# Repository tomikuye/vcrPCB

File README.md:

# vcrPCB
KiCad PCB files and gerbers for custom PCB for Rice The Glove Team

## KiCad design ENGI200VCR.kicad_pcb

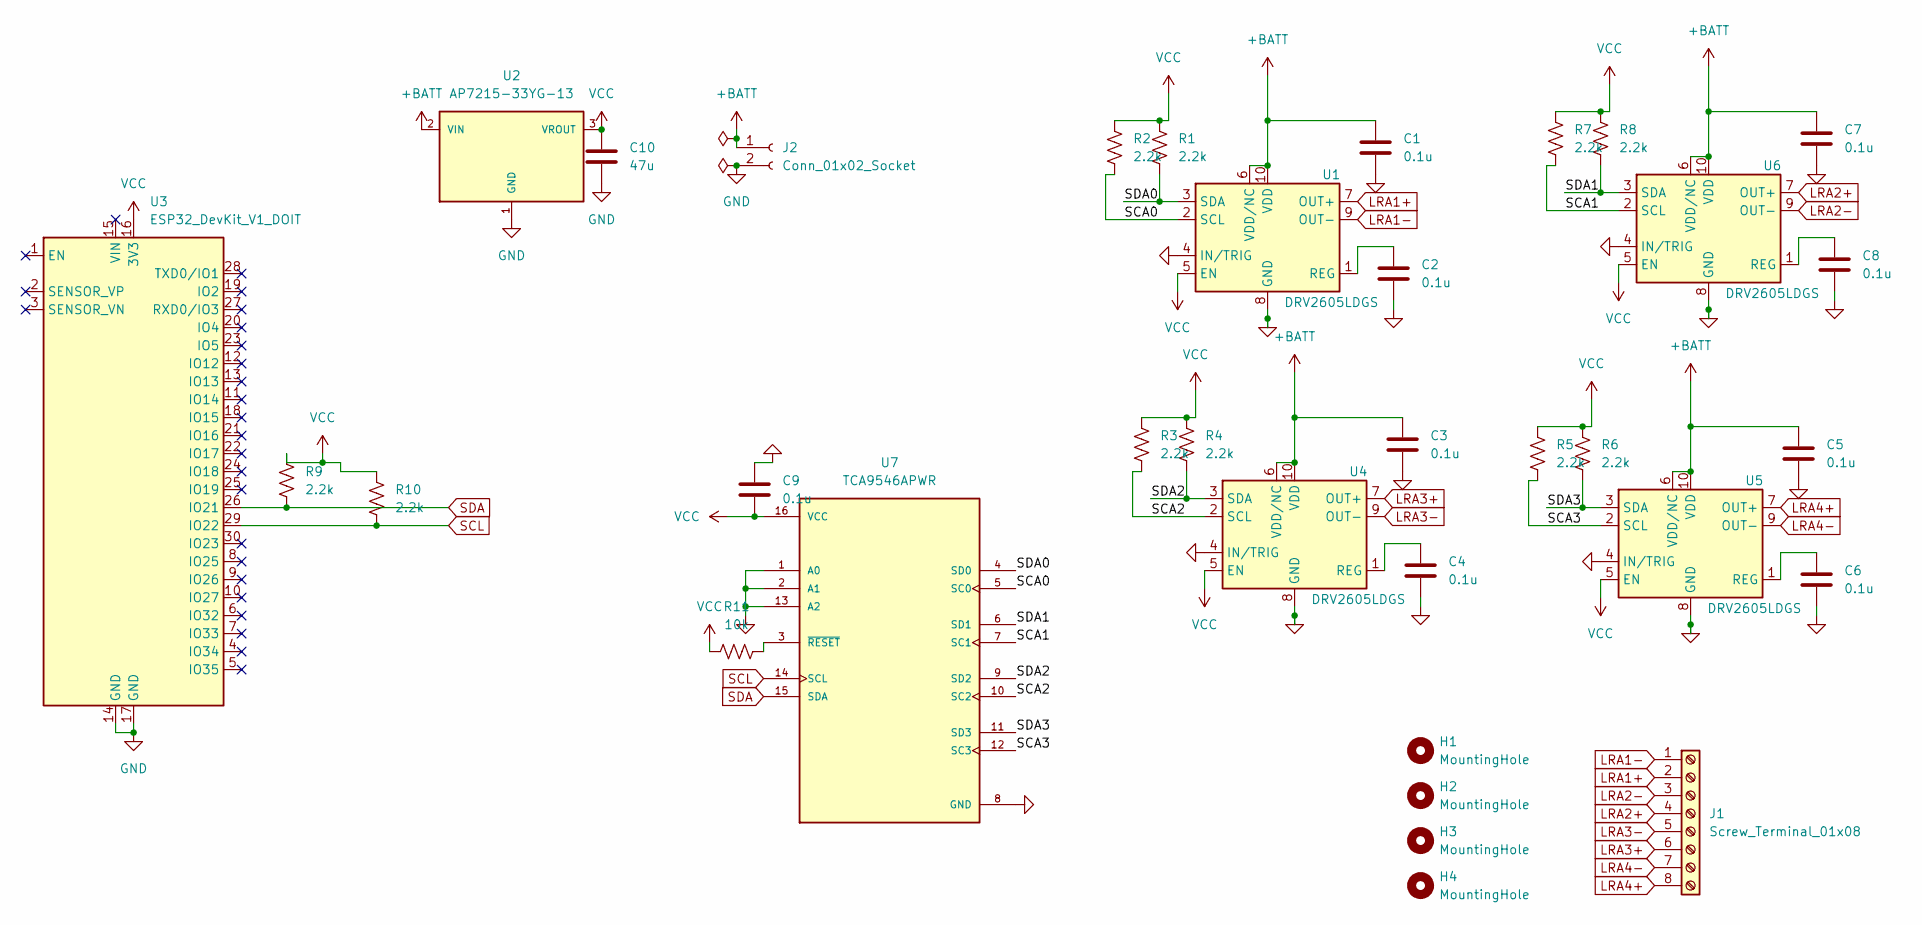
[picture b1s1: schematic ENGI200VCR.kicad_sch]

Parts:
C1, C2, C3, C4, C5, C6, C7, C8, C9: 0.1u; C_0402_1005Metric
C10: 47u; C_0805_2012Metric
H1, H2, H3, H4: MountingHole; MountingHole_2.2mm_M2
J1: Screw_Terminal_01x08; TerminalBlock_bornier-8_P5.08mm
J2: Conn_01x02_Socket; JST_EH_B2B-EH-A_1x02_P2.50mm_Vertical
R1, R2, R3, R4, R5, R6, R7, R8, R9, R10: 2.2k; R_0402_1005Metric
R11: 10k; R_0402_1005Metric
U1, U4, U5, U6: DRV2605LDGS; VSSOP-10_3x3mm_P0.5mm
U2: AP7215-33YG-13; SOT150P400X160-3N; MPN AP7215-33YG-13
U3: ESP32_DevKit_V1_DOIT; esp32_devkit_v1_doit
U7: TCA9546APWR; SOP65P640X120-16N; PARTREV B

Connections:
+BATT: C1.1, C3.1, C5.1, C7.1, J2.1, U1.6 (VDD/NC), U1.10 (VDD), U2.2 (VIN), U4.6 (VDD/NC), U4.10 (VDD), U5.6 (VDD/NC), U5.10 (VDD), U6.6 (VDD/NC), U6.10 (VDD)
/SCA0: R2.2, U1.2 (SCL), U7.5 (SC0)
/SCA1: R7.2, U6.2 (SCL), U7.7 (SC1)
/SCA2: R3.2, U4.2 (SCL), U7.10 (SC2)
/SCA3: R5.2, U5.2 (SCL), U7.12 (SC3)
/SDA0: R1.2, U1.3 (SDA), U7.4 (SD0)
/SDA1: R8.2, U6.3 (SDA), U7.6 (SD1)
/SDA2: R4.2, U4.3 (SDA), U7.9 (SD2)
/SDA3: R6.2, U5.3 (SDA), U7.11 (SD3)
GND: C1.2, C2.2, C3.2, C4.2, C5.2, C6.2, C7.2, C8.2, C9.1, C10.2, J2.2, U1.4 (IN/TRIG), U1.8 (GND), U2.1 (GND), U3.14 (GND), U3.17 (GND), U4.4 (IN/TRIG), U4.8 (GND), U5.4 (IN/TRIG), U5.8 (GND), U6.4 (IN/TRIG), U6.8 (GND), U7.1 (A0), U7.2 (A1), U7.8 (GND), U7.13 (A2); also elsewhere on the board
LRA1+: J1.2, U1.7 (OUT+)
LRA1-: J1.1, U1.9 (OUT-)
LRA2+: J1.4, U6.7 (OUT+)
LRA2-: J1.3, U6.9 (OUT-)
LRA3+: J1.6, U4.7 (OUT+)
LRA3-: J1.5, U4.9 (OUT-)
LRA4+: J1.8, U5.7 (OUT+)
LRA4-: J1.7, U5.9 (OUT-)
unnamed: C2.1, U1.1 (REG)
unnamed: C4.1, U4.1 (REG)
unnamed: C6.1, U5.1 (REG)
unnamed: C8.1, U6.1 (REG)
unnamed: R11.2, U7.3 (~RESET)
SCL: R10.2, U3.29 (IO22), U7.14 (SCL)
SDA: R9.2, U3.26 (IO21), U7.15 (SDA)
VCC: C9.2, C10.1, R1.1, R2.1, R3.1, R4.1, R5.1, R6.1, R7.1, R8.1, R9.1, R10.1, R11.1, U1.5 (EN), U2.3 (VROUT), U3.16 (3V3), U4.5 (EN), U5.5 (EN), U6.5 (EN), U7.16 (VCC); also elsewhere on the board

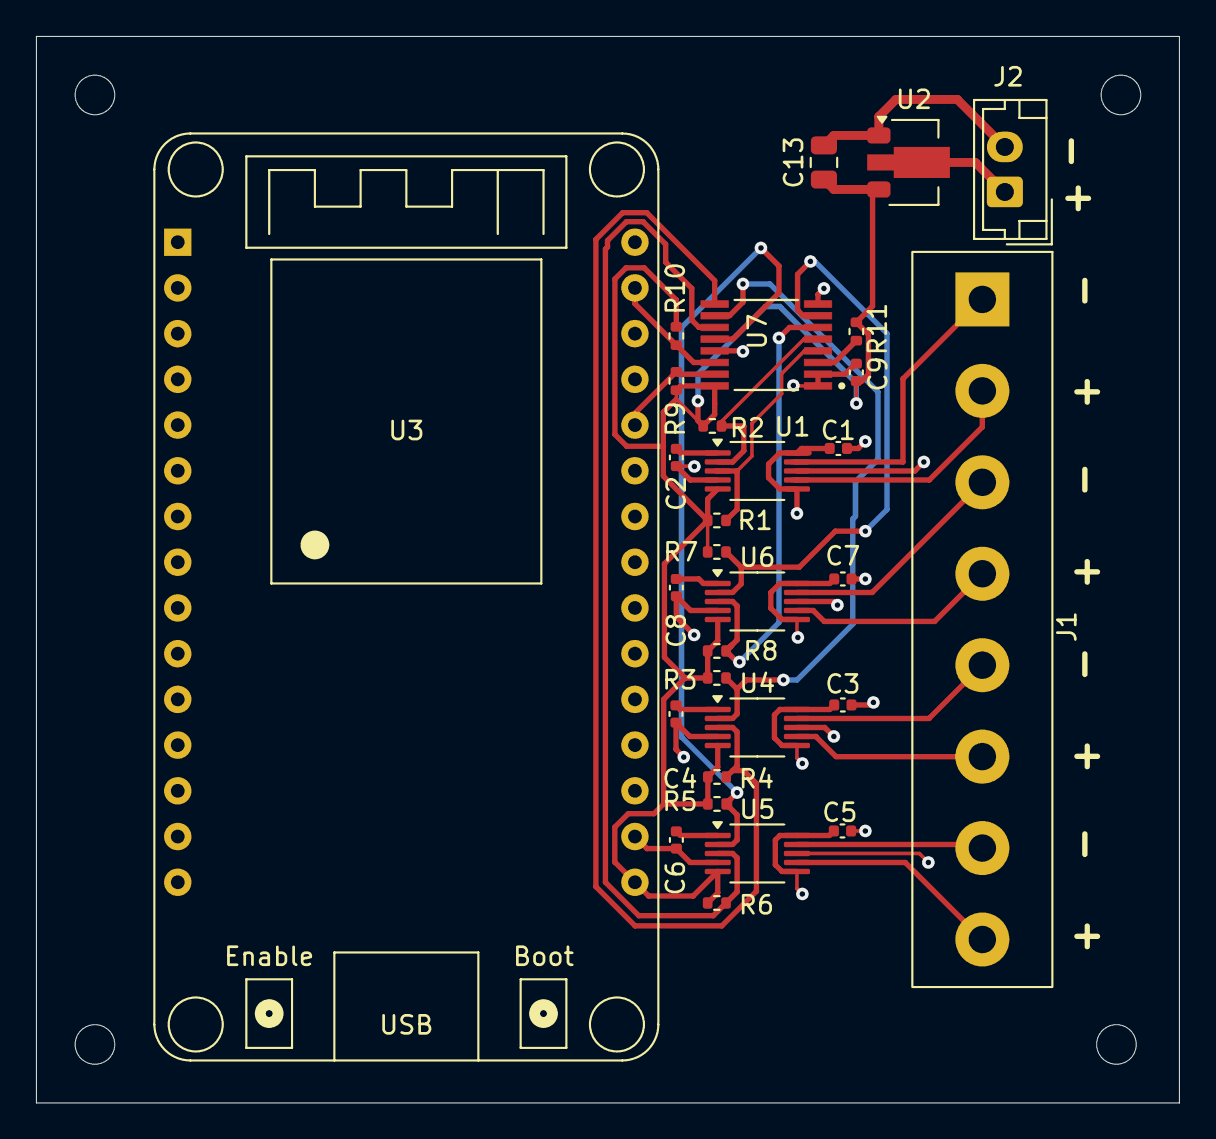
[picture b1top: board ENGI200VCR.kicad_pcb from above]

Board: 4 copper layers, 63.5 x 59.2 mm, 34 parts (0 on the bottom side), 26 nets.

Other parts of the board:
C13: 47u; C_0805_2012Metric

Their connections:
GND: C13.2; also elsewhere on the board
VCC: C13.1; also elsewhere on the board

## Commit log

2024-04-01 Rename Screenshot 2024-04-01 at 2.46.02 PM.png to 3DRenderofPCB
2024-04-01 Rename Screenshot 2024-04-01 at 2.47.38 PM.png to PCBTraceView
